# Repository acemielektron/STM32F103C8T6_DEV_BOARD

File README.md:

# STM32F103C8T6_DEV_BOARD

Single sided DIY PCB for STM32F103C8T6

There are many pcb designs for stm32f103C8T6 what makes this design special is:
- it's single sided
- minimum number of bridges at top side (only one bridge)
so it's very diy friendly (I think).

Here is photos of earlier version:
Bottom side</img>
Top side</img>

And here images of pcb and schematic
pcb</img>
schematic</img>

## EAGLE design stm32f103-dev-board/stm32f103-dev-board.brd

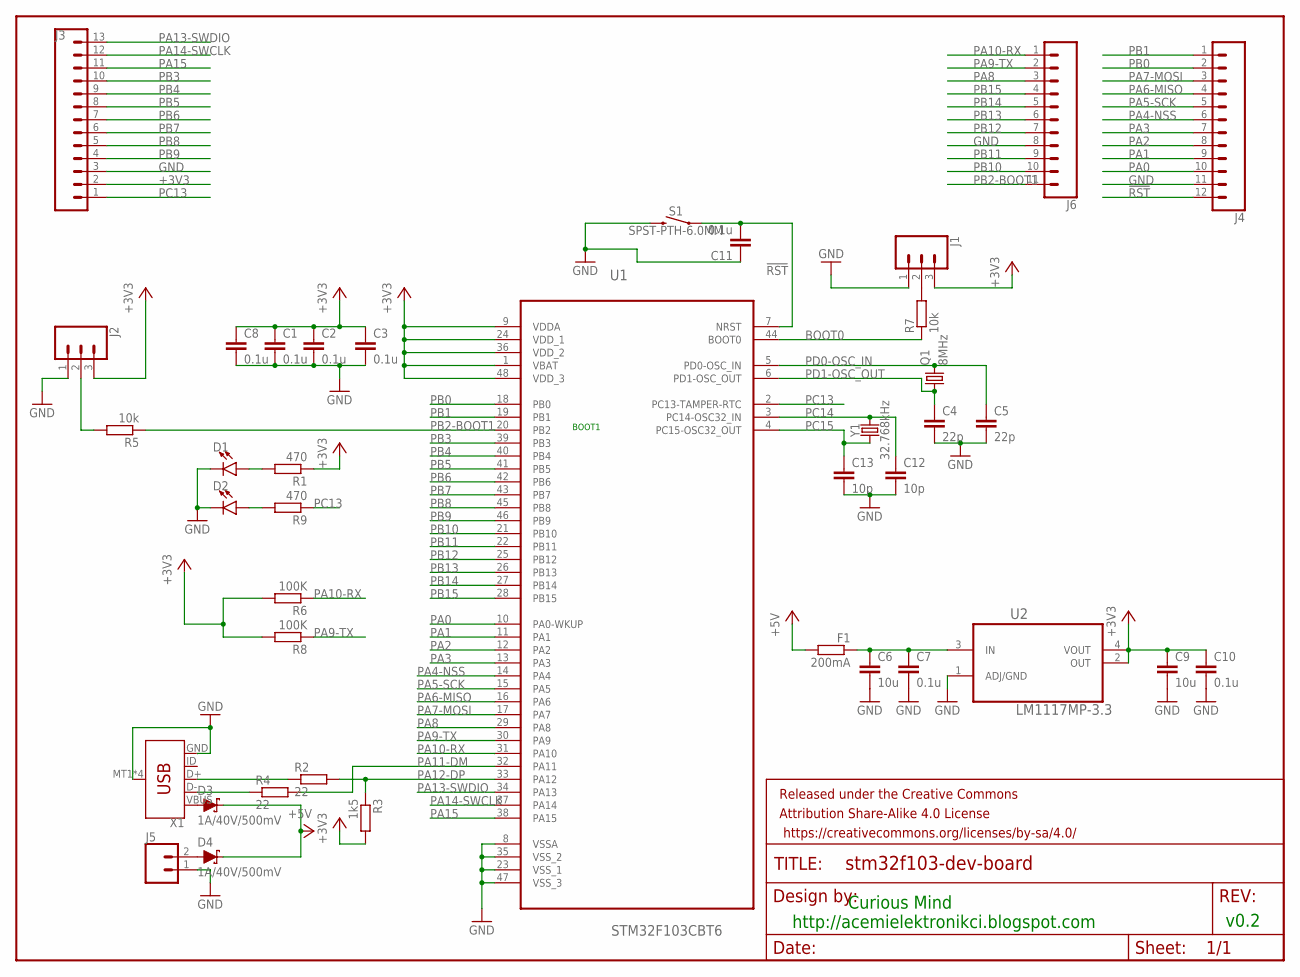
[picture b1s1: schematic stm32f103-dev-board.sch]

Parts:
C1, C2, C3, C7, C8, C10, C11: 0.1u; C0805K
C4, C5: 22p; C0805K
C6, C9: 10u; C0805K
C12, C13: 10p; C1206K
D1, D2: LED3MM; LED_3MM
D3, D4: 1A/40V/500mV; SMA-DIODE
F1: 200mA; R0805
FRAME1: FRAME-LETTER; CREATIVE_COMMONS
J1, J2: CONN_03; 1X03
J3: CONN_13; 1X13
J4: CONN_12; 1X12
J5: CONN_02; 1X02
J6: CONN_11; 1X11
Q1: 8MHz; HC49/S
R1, R9: 470; R0805
R2, R4: 22; R0805
R3: 1k5; R1206
R5, R7: 10k; R0805
R6, R8: 100K; R0805
S1: SPST-PTH-6.0MM; TACTILE_SWITCH_PTH_6.0MM
U1: STM32F103CBT6; QFP50P900X900X160-48N
U2: LM1117MP-3.3; SOT230P696X180-4N
X1: USB_MICRO-B_SMT; USB-MICROB
Y1: 32.768kHz; CRYSTAL-SMD-2X6-CYL

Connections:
!RST: C11.2, J4.12, S1.1, U1.7 (NRST)
+3V3: C1.1, C2.1, C3.1, C8.1, C9.1, C10.1, J1.3, J2.3, J3.2, R1.1, R3.2, R6.2, R8.2, U1.1 (VBAT), U1.9 (VDDA), U1.24 (VDD_1), U1.36 (VDD_2), U1.48 (VDD_3), U2.2 (OUT), U2.4 (VOUT)
+5V: D3.C, D4.C, F1.2
BOOT0: R7.1, U1.44 (BOOT0)
GND: C1.2, C2.2, C3.2, C4.2, C5.2, C6.2, C7.2, C8.2, C9.2, C10.2, C11.1, C12.2, C13.2, D1.K (C), D2.K (C), J1.1, J2.1, J3.3, J4.11, J5.1, J6.8, S1.3 (2), U1.8 (VSSA), U1.23 (VSS_1), U1.35 (VSS_2), U1.47 (VSS_3), U2.1 (ADJ/GND), X1.GND, X1.MT1 (SHIELD), X1.MT2 (SHIELD), X1.P$1 (SHIELD), X1.P$2 (SHIELD)
unnamed: D3.A, X1.VBUS
unnamed: D2.A, R9.2
unnamed: D1.A, R1.2
unnamed: J1.2, R7.2
unnamed: D4.A, J5.2
unnamed: C6.1, C7.1, F1.1, U2.3 (IN)
unnamed: R4.1, X1.D-
unnamed: R2.1, X1.D+
unnamed: J2.2, R5.2
PA0: J4.10, U1.10 (PA0-WKUP)
PA1: J4.9, U1.11 (PA1)
PA2: J4.8, U1.12 (PA2)
PA3: J4.7, U1.13 (PA3)
PA4-NSS: J4.6, U1.14 (PA4)
PA5-SCK: J4.5, U1.15 (PA5)
PA6-MISO: J4.4, U1.16 (PA6)
PA7-MOSI: J4.3, U1.17 (PA7)
PA8: J6.3, U1.29 (PA8)
PA9-TX: J6.2, R8.1, U1.30 (PA9)
PA10-RX: J6.1, R6.1, U1.31 (PA10)
PA11-DM: R4.2, U1.32 (PA11)
PA12-DP: R2.2, R3.1, U1.33 (PA12)
PA13-SWDIO: J3.13, U1.34 (PA13)
PA14-SWCLK: J3.12, U1.37 (PA14)
PA15: J3.11, U1.38 (PA15)
PB0: J4.2, U1.18 (PB0)
PB1: J4.1, U1.19 (PB1)
PB2-BOOT1: J6.11, R5.1, U1.20 (PB2)
PB3: J3.10, U1.39 (PB3)
PB4: J3.9, U1.40 (PB4)
PB5: J3.8, U1.41 (PB5)
PB6: J3.7, U1.42 (PB6)
PB7: J3.6, U1.43 (PB7)
PB8: J3.5, U1.45 (PB8)
PB9: J3.4, U1.46 (PB9)
PB10: J6.10, U1.21 (PB10)
PB11: J6.9, U1.22 (PB11)
PB12: J6.7, U1.25 (PB12)
PB13: J6.6, U1.26 (PB13)
PB14: J6.5, U1.27 (PB14)
PB15: J6.4, U1.28 (PB15)
PC13: J3.1, R9.1, U1.2 (PC13-TAMPER-RTC)
PC14: C12.1, U1.3 (PC14-OSC32_IN), Y1.X2 (2)
PC15: C13.1, U1.4 (PC15-OSC32_OUT), Y1.X1 (1)
PD0-OSC_IN: C5.1, Q1.2, U1.5 (PD0-OSC_IN)
PD1-OSC_OUT: C4.1, Q1.1, U1.6 (PD1-OSC_OUT)

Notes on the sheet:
BOOT1
Curious Mind http://acemielektronikci.blogspot.com
v0.2

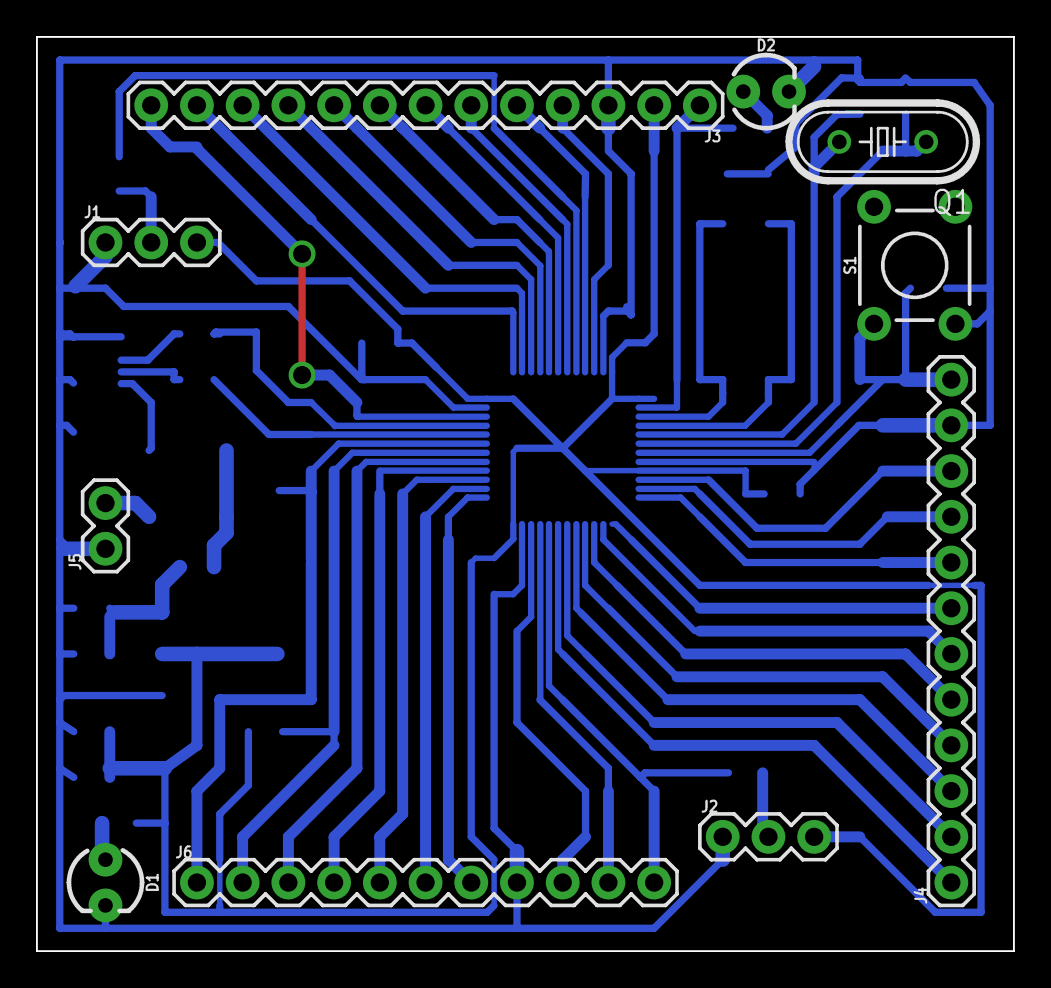
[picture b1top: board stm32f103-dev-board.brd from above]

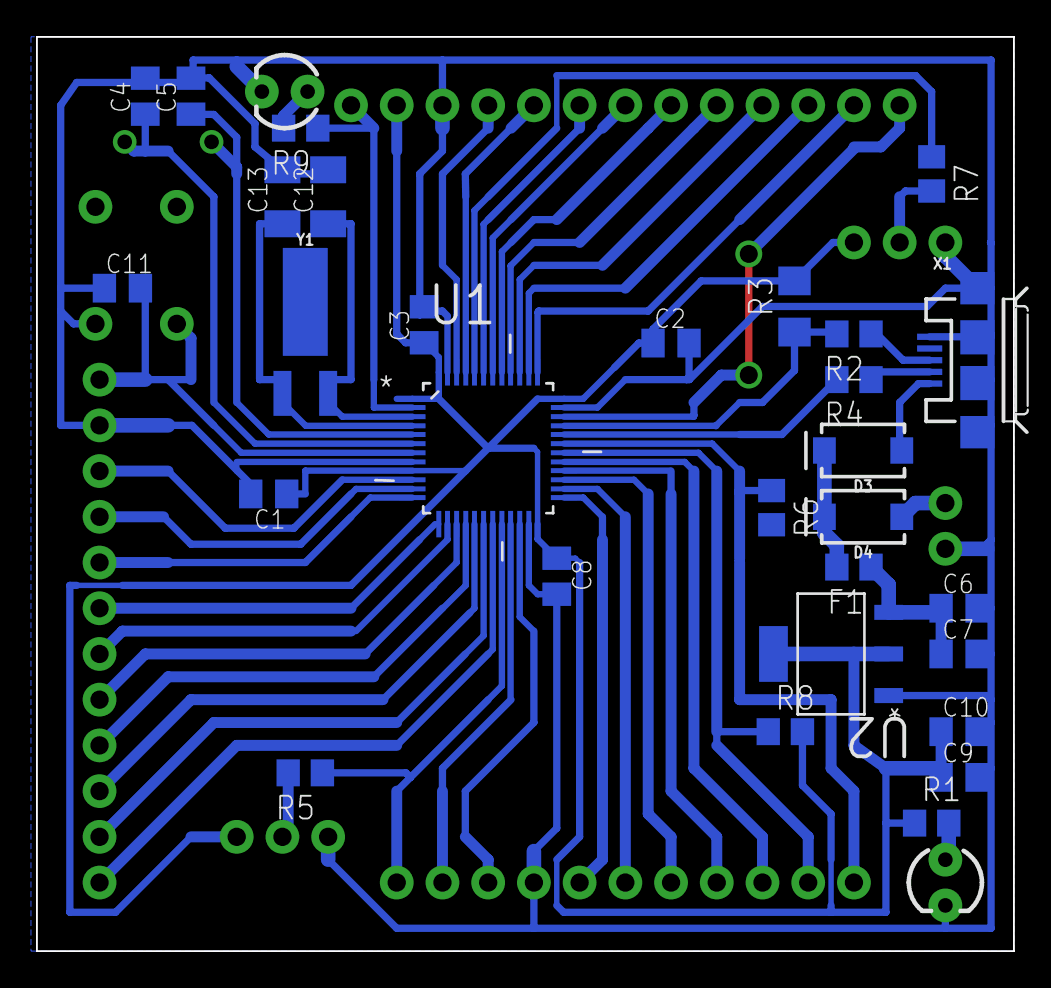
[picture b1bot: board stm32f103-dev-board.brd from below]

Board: 2 copper layers, 54.3 x 50.8 mm, 40 parts (29 on the bottom side), 51 nets.

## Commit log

2019-02-14 stm32f103c8t6 dev board
    Eagle files
2019-02-15 v0.2
    added led on PC13
    added power led
    added external power in
2019-02-17 error
2019-02-17 corrected usb pullup
    corrected usb pullup
    routed swdio (PA13)
2019-02-17 v0.3
2019-02-17 v0.35 optimization
2019-02-18 v0.15
    My first stm32f1 diy board
    Works with arduino ide using "generic_boot20_pc13.bin"
2019-07-24 Create LICENSE
2019-07-24 Update LICENSE
    Creative Commons Attribution-ShareAlike 3.0
2019-07-24 Update LICENSE
2019-07-24 Cleanup
2022-02-11 Put eagle files in folder
    Put eagle files in stm32f103-dev-board folder

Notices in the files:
README.md:
CC BY-SA 4.0
parts and their libraries:
SparkFun-Connectors: Licensing: Creative Commons ShareAlike 4.0 International - https://creativecommons.org/licenses/by-sa/4.0
SparkFun-Aesthetics: Released under the Creative Commons Attribution Share-Alike 4.0 License
SparkFun-Aesthetics: https://creativecommons.org/licenses/by-sa/4.0
